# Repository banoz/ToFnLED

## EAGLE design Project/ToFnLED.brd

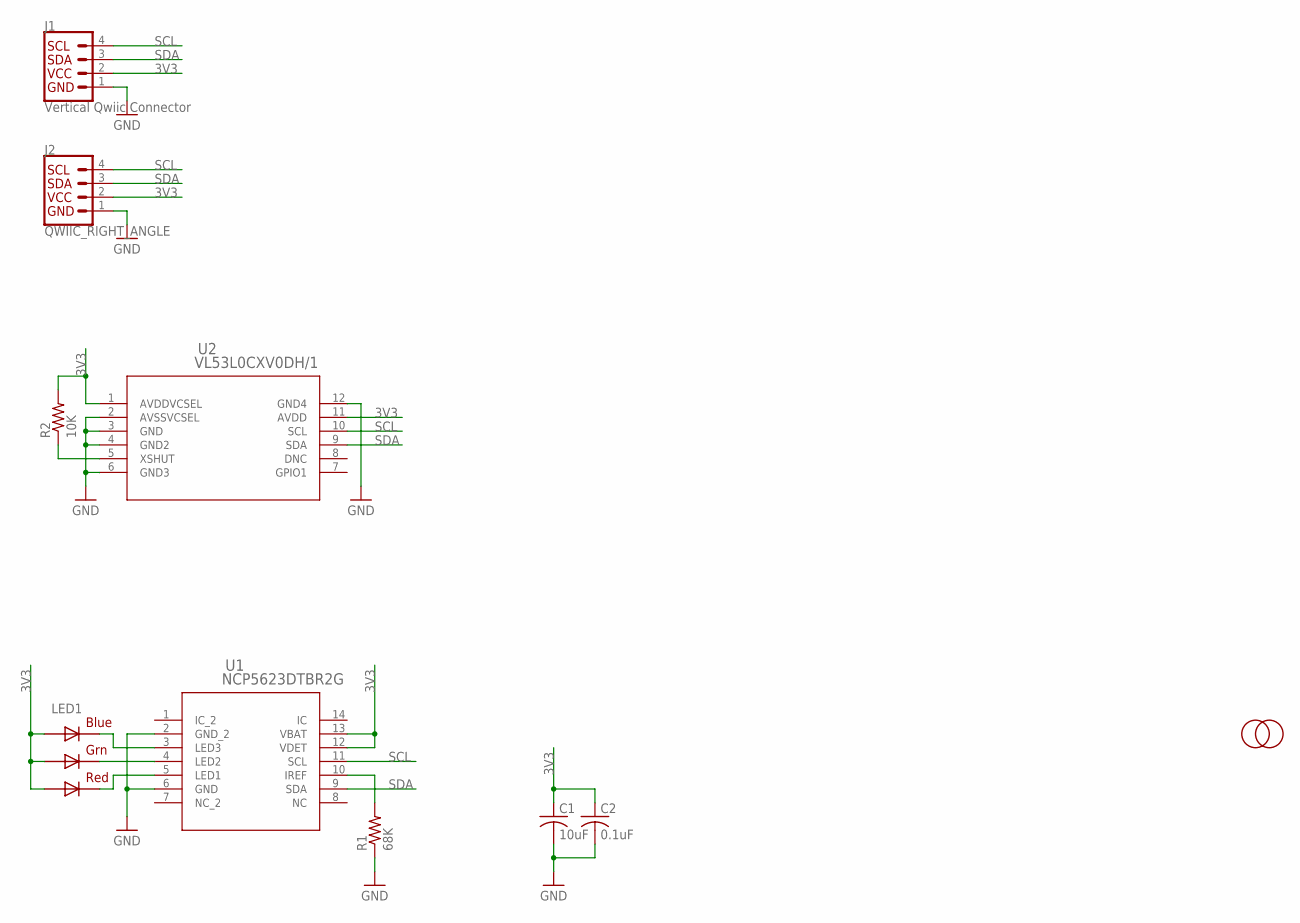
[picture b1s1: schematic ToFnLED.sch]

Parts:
C1: 10uF; C0603; LCSC C19702
C2: 0.1uF; C0603; LCSC C1591
J1: Vertical Qwiic Connector; JST04_1MM_VERT; LCSC C160390
J2: QWIIC_RIGHT_ANGLE; JST04_1MM_RA; LCSC C160404
LED1: RGBLED5050; LCSC C784540
R1: 68K; R0603; LCSC C114633
R2: 10K; R0603; LCSC C98220
U1: NCP5623DTBR2G; TSSOP-14_ONS; LCSC C904521
U2: VL53L0CXV0DH/1; LGA12_STM; LCSC C91199
U$1, U$2: FIDUCIAL; FIDUCIAL_1MM

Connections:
3V3: C1.1, C2.1, J1.2, J2.2, LED1.1 (GREEN_A), LED1.2 (RED_A), LED1.3 (BLUE_A), R2.2, U1.12 (VDET), U1.13 (VBAT), U2.1 (AVDDVCSEL), U2.11 (AVDD)
GND: C1.2, C2.2, J1.1, J2.1, R1.1, U1.2 (GND_2), U1.6 (GND), U2.2 (AVSSVCSEL), U2.3 (GND), U2.4 (GND2), U2.6 (GND3), U2.12 (GND4)
LED1: LED1.5 (RED_C), U1.5 (LED1)
LED2: LED1.6 (GREEN_C), U1.4 (LED2)
LED3: LED1.4 (BLUE_C), U1.3 (LED3)
unnamed: R1.2, U1.10 (IREF)
unnamed: R2.1, U2.5 (XSHUT)
SCL: J1.4, J2.4, U1.11 (SCL), U2.10 (SCL)
SDA: J1.3, J2.3, U1.9 (SDA), U2.9 (SDA)

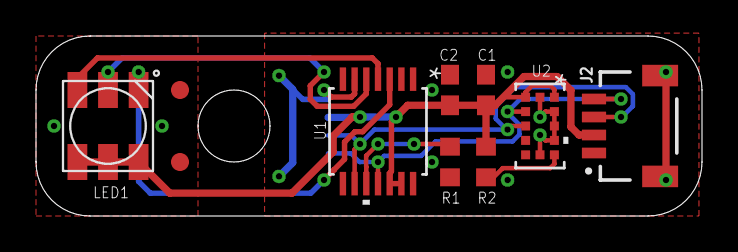
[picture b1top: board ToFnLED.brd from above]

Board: 2 copper layers, 37.0 x 10.0 mm, 11 parts (1 on the bottom side), 9 nets.

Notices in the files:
parts and their libraries:
SparkFun-Connectors: Licensing: Creative Commons ShareAlike 4.0 International - https://creativecommons.org/licenses/by-sa/4.0
COPYRIGHT: Copyright (C) 2022 Ultra Librarian. All rights reserved.
